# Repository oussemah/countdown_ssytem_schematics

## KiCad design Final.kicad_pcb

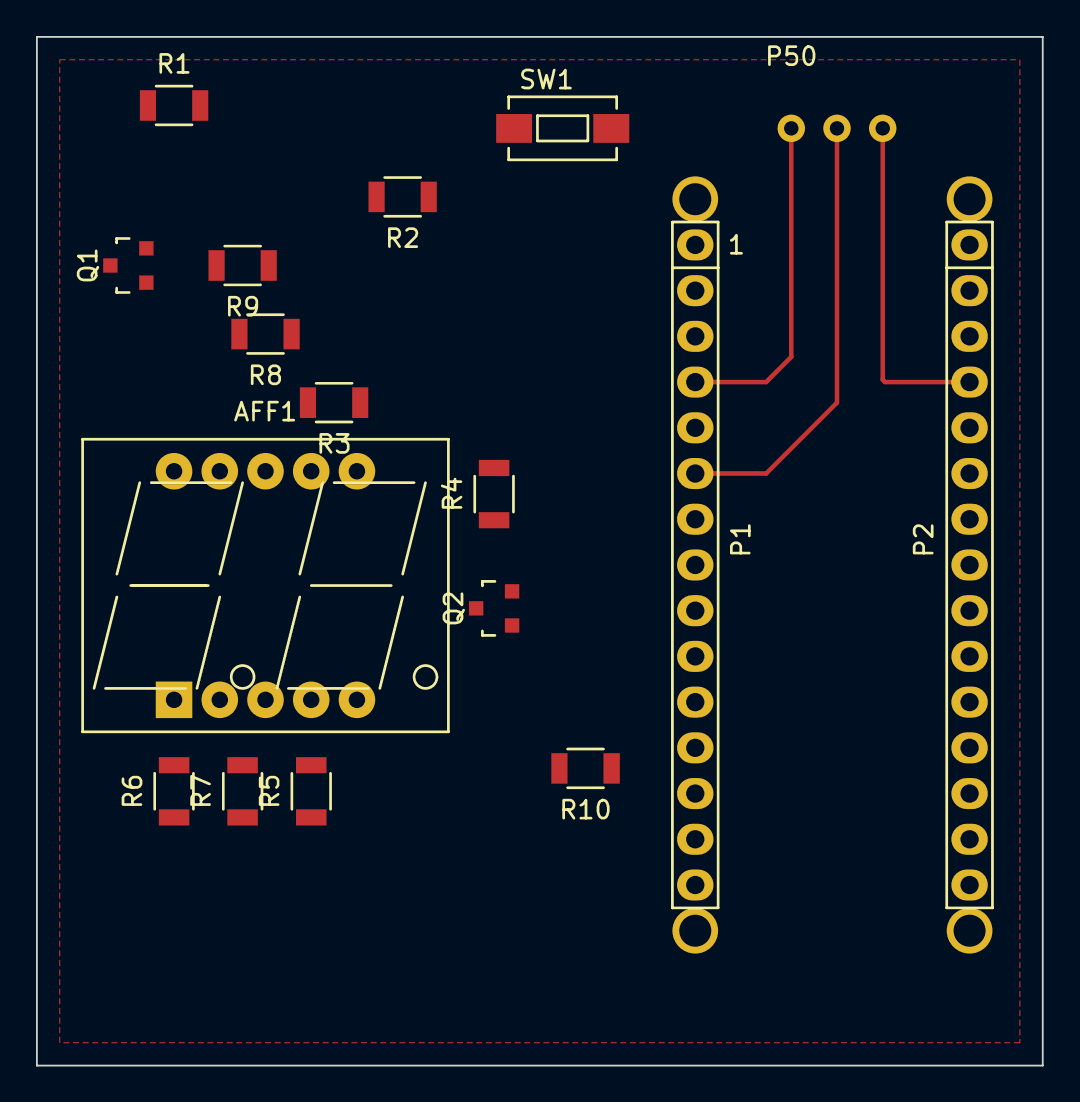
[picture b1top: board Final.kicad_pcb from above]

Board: 2 copper layers, 55.9 x 57.2 mm, 21 parts (0 on the bottom side), 25 nets.

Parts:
AFF1: ELD-426x
P1: Digital; Socket_Strip_Arduino_1x15
P2: Analog; Socket_Strip_Arduino_1x15
P3: CONN RELAY; 1pin_Nano
P4, P5, P6: CONN_1; 1pin_Nano
P50: REL_CONN; TO-92_Inline_Wide
Q1, Q2: FMMT3906; SOT-23
R1: 1KOhm; R_1206
R2, R3, R4, R5, R6, R7, R8, R9, R10: 100; R_1206
SW1: SW_PUSH; SW_SPST_EVQPE1

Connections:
+5V: P2.4, P50.3, Q1.1, Q2.1, R1.1
/2: P1.5, R1.2, SW1.1
/3(**): P1.6, P50.2
/4: P1.7, R2.1
/5(**): P1.8, R9.1
/6(**): P1.9, R8.1
/7: P1.10, R3.1
/8: P1.11, R4.1
/9(**): P1.12, R10.1
/10(**/SS): P1.13, R5.1
/11(**/MISO): P1.14, R7.1
/12(MOSI): P1.15, R6.1
/Reset: P1.3, P2.3
GND: P1.4, P2.2, P3.1, P50.1, SW1.2
unnamed: AFF1.1, R6.2
unnamed: AFF1.3, R7.2
unnamed: AFF1.4, R5.2
unnamed: AFF1.5, Q2.3
unnamed: AFF1.6, R4.2
unnamed: AFF1.7, R3.2
unnamed: AFF1.8, R8.2
unnamed: AFF1.9, R9.2
unnamed: AFF1.10, Q1.3
unnamed: Q1.2, R2.2
unnamed: Q2.2, R10.2

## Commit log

2016-03-09 SMD not finished yet
2016-03-09 Adding library install script
